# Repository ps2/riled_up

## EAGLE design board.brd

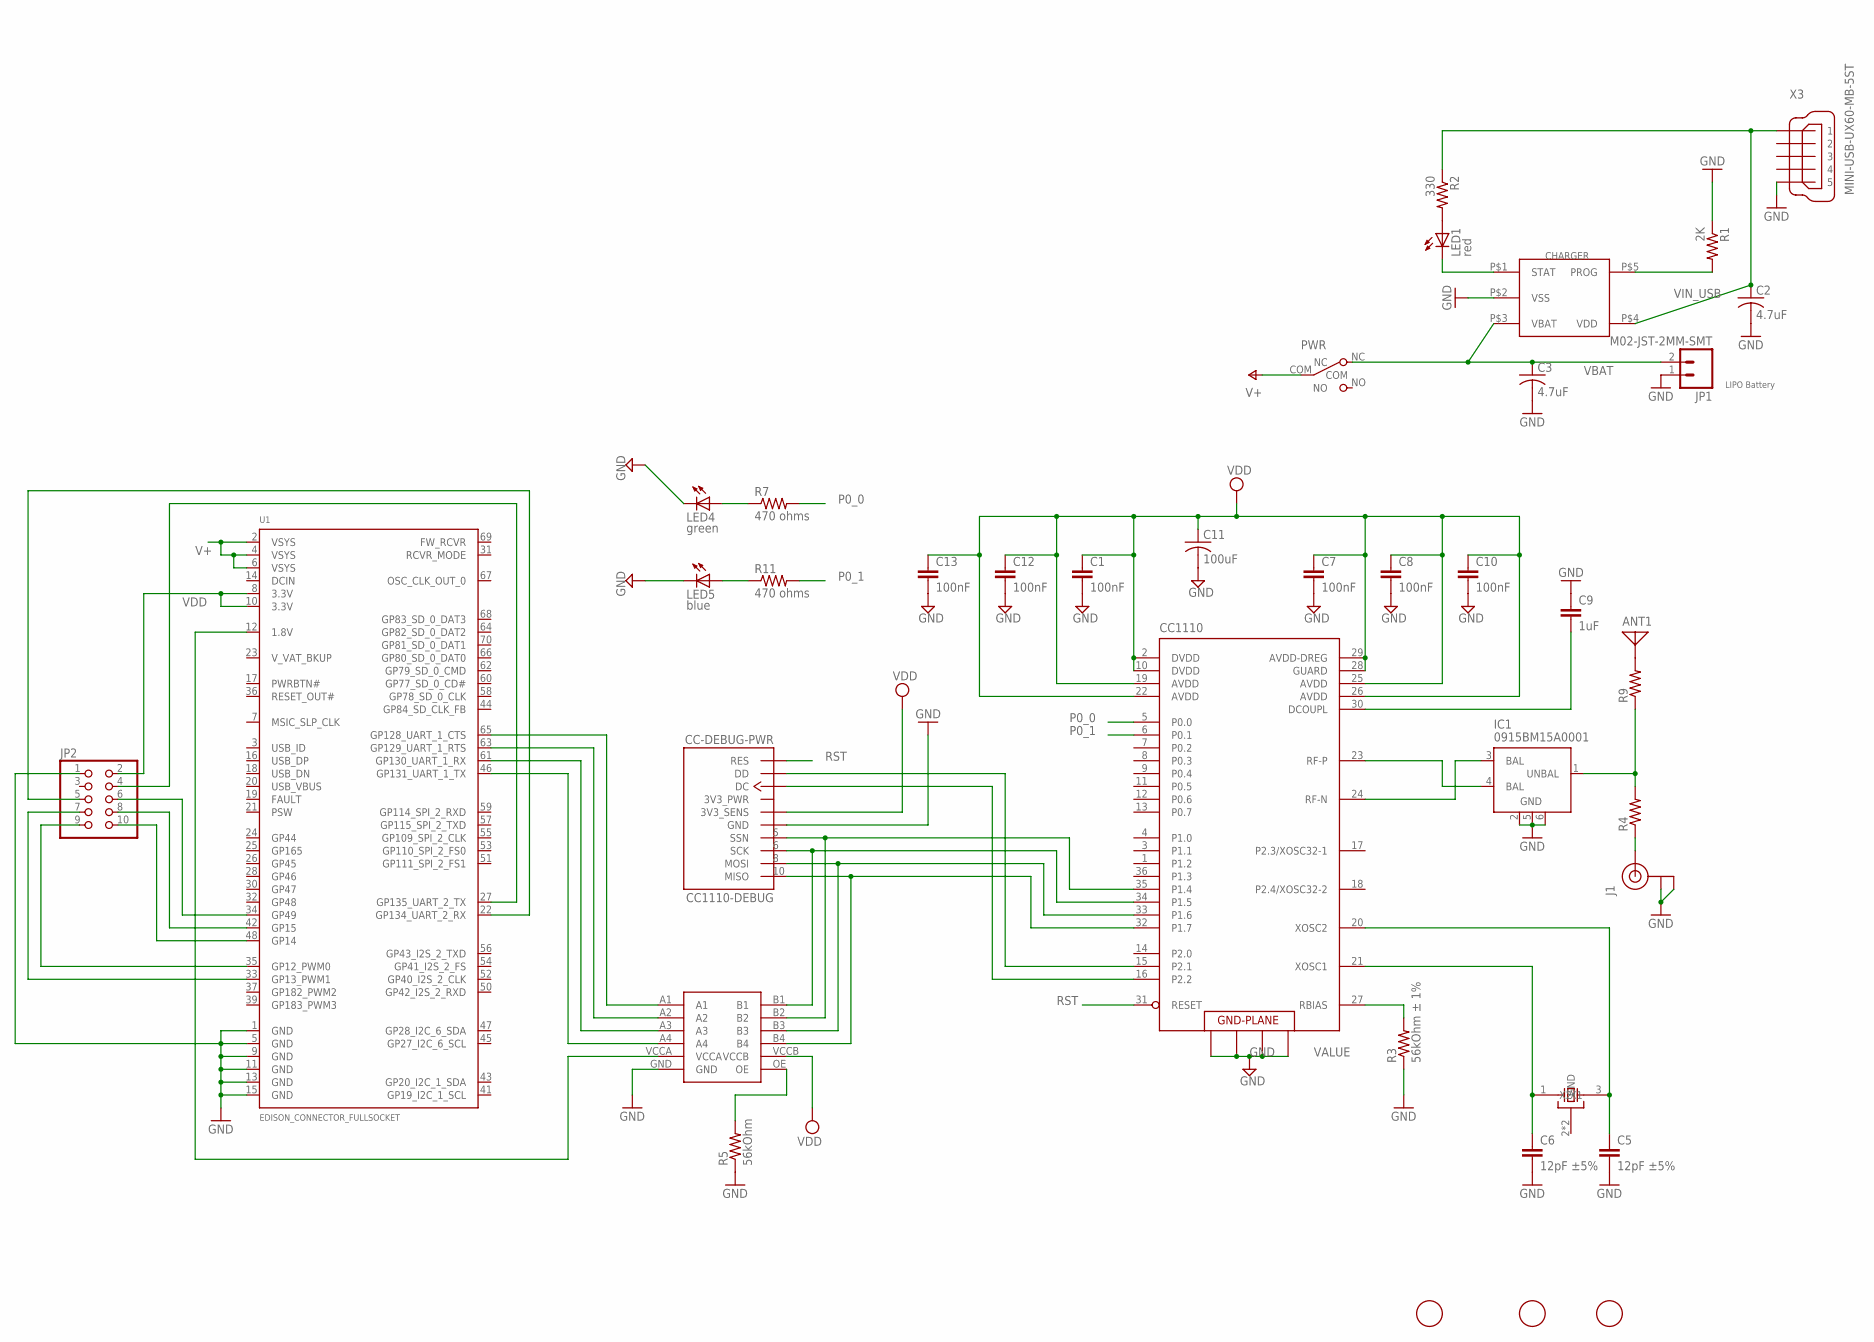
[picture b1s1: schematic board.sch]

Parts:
ANT1: ANTENNA; PAD-01
C1, C7, C8, C10, C12, C13: 100nF; C0402
C2, C3: 4.7uF; C0603K
C5, C6: 12pF ±5%; C0402K
C9: 1uF; C0402K
C11: 100uF; C0805K
CC1110: CC1110; QLP-36_UPDATE
CC1110-DEBUG: CC-DEBUG-PWR; CC-P05
CHARGER: MCP73831; 5PIN_SOT23
FID1, FID2, FID3: FIDUCIAL; FIDUCIAL_1MM
IC1: 0915BM15A0001
J1: U.FL
JP1: M02-JST-2MM-SMT; JST-2-SMD
JP2: PINHD-2X5; 2X05
LED1: red; SML0603
LED4: green; SML0603
LED5: blue; SML0603
PWR: SW_SLIDE; SLIDE_SWITCH_SMD
R1: 2K; R0402
R2: 330; R0402
R3: 56kOhm ± 1%; R0402
R4, R9: R-US_R0402; R0402
R5: 56kOhm; R0402
R7, R11: 470 ohms; R0402
U1: EDISON_CONNECTOR_FULLSOCKET; DF40-XC-(X.X)-70DS-0.4V(51)
U$1: TXB0104; VQFN-N14
X1: 24MHz 8pF 10ppm -20C +70C; CTS_32X25
X3: MINI-USB-UX60-MB-5ST; UX60-MB-5ST

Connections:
DC: CC1110.16 (P2.2), CC1110-DEBUG.3 (DC)
DD: CC1110.15 (P2.1), CC1110-DEBUG.4 (DD)
GND: C1.2, C2.2, C3.2, C5.2, C6.2, C7.2, C8.2, C9.1, C10.2, C11.2, C12.2, C13.2, CC1110.37 (GND), CC1110.38 (GND), CC1110.39 (GND), CC1110.40 (GND), CC1110-DEBUG.1 (GND), CHARGER.P$2 (VSS), IC1.2 (GND), IC1.5 (GND), IC1.6 (GND), J1.P$1 (GND), J1.P$2 (GND), JP1.1 (2), JP2.1, LED4.C, LED5.C, R1.1, R3.1, R5.1, U1.1 (GND), U1.5 (GND), U1.9 (GND), U1.11 (GND), U1.13 (GND), U1.15 (GND), U$1.GND, X1.2 (GND), X1.4 (GND), X3.5
MISO: CC1110.32 (P1.7), CC1110-DEBUG.10 (MISO), U$1.B4
MOSI: CC1110.33 (P1.6), CC1110-DEBUG.8 (MOSI), U$1.B3
unnamed: U1.46 (GP131_UART_1_TX), U$1.A4
unnamed: CHARGER.P$1 (STAT), LED1.C
unnamed: CHARGER.P$5 (PROG), R1.2
unnamed: LED1.A, R2.2
unnamed: CC1110.24 (RF-N), IC1.3 (BAL)
unnamed: U1.61 (GP130_UART_1_RX), U$1.A3
unnamed: CC1110.23 (RF-P), IC1.4 (BAL)
unnamed: J1.P$3 (SIGNAL), R4.1
unnamed: IC1.1 (UNBAL), R4.2, R9.1
unnamed: U1.63 (GP129_UART_1_RTS), U$1.A2
unnamed: ANT1.1, R9.2
unnamed: U1.65 (GP128_UART_1_CTS), U$1.A1
unnamed: CC1110.27 (RBIAS), R3.2
unnamed: U1.12 (1.8V), U$1.VCCA
unnamed: R5.2, U$1.OE
unnamed: JP2.9, U1.35 (GP12_PWM0)
unnamed: C9.2, CC1110.30 (DCOUPL)
unnamed: JP2.7, U1.33 (GP13_PWM1)
unnamed: C6.1, CC1110.21 (XOSC1), X1.1 (X1)
unnamed: C5.1, CC1110.20 (XOSC2), X1.3 (X2)
unnamed: JP2.10, U1.48 (GP14)
unnamed: JP2.8, U1.42 (GP15)
unnamed: LED4.A, R7.1
unnamed: LED5.A, R11.1
unnamed: JP2.6, U1.34 (GP49)
unnamed: JP2.4, U1.27 (GP135_UART_2_TX)
unnamed: JP2.5, U1.22 (GP134_UART_2_RX)
P0_0: CC1110.5 (P0.0), R7.2
P0_1: CC1110.6 (P0.1), R11.2
RST: CC1110.31 (RESET), CC1110-DEBUG.7 (RES)
SCK: CC1110.34 (P1.5), CC1110-DEBUG.6 (SCK), U$1.B1
SSN: CC1110.35 (P1.4), CC1110-DEBUG.5 (SSN), U$1.B2
V+: PWR.COM, U1.2 (VSYS), U1.4 (VSYS), U1.6 (VSYS)
VBAT: C3.1, CHARGER.P$3 (VBAT), JP1.2 (1), PWR.NC
VDD: C1.1, C7.1, C8.1, C10.1, C11.1, C12.1, C13.1, CC1110.2 (DVDD), CC1110.10 (DVDD), CC1110.19 (AVDD), CC1110.22 (AVDD), CC1110.25 (AVDD), CC1110.26 (AVDD), CC1110.28 (GUARD), CC1110.29 (AVDD-DREG), CC1110-DEBUG.2 (3V3_SENS), JP2.2, U1.8 (3.3V), U1.10 (3.3V), U$1.VCCB
VIN_USB: C2.1, CHARGER.P$4 (VDD), R2.1, X3.1

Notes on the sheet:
LIPO Battery

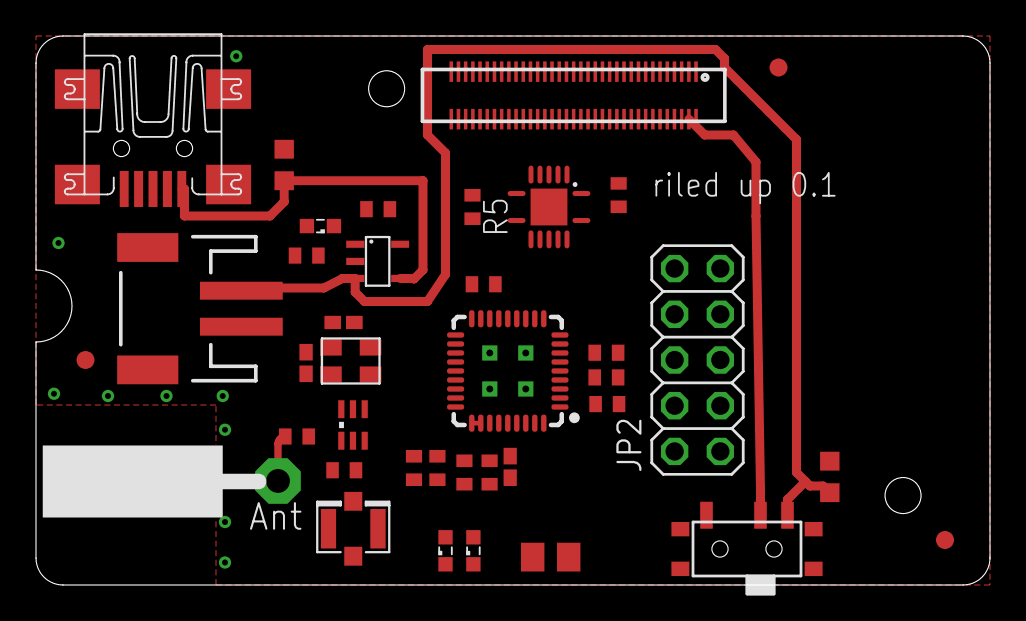
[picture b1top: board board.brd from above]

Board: 2 copper layers, 53.0 x 30.5 mm, 39 parts (1 on the bottom side), 41 nets.

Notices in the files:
parts and their libraries:
parts: Package design from "pretty-eagle-libs" at https://github.com/esden/pretty-eagle-libs/blob/master/pel_misc.lbr by @esden at Github. (CC-BY-SA-3.0)
SparkFun-Connectors: Licensing: Creative Commons ShareAlike 4.0 International - https://creativecommons.org/licenses/by-sa/4.0
